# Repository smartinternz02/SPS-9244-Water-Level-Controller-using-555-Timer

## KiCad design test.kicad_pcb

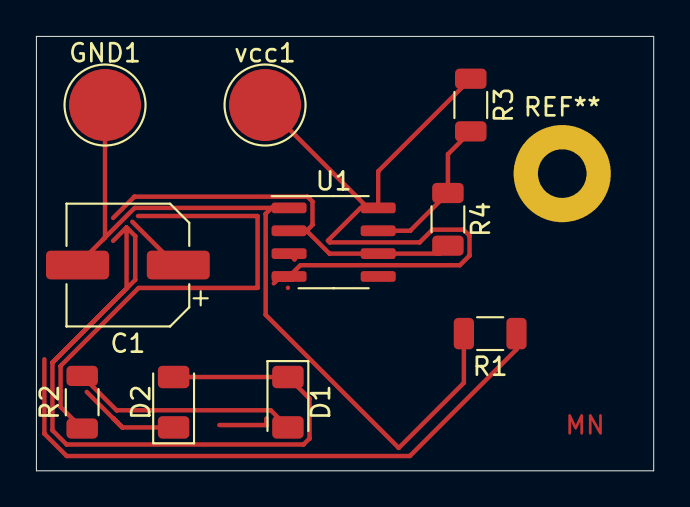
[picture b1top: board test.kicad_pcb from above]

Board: 2 copper layers, 34.3 x 24.1 mm, 10 parts (0 on the bottom side), 7 nets.

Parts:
C1: 10ufd/16V; CP_Elec_6.3x5.2
D1, D2: LED; LED_1206_3216Metric
GND1: GND; TestPoint_Pad_D4.0mm
R1, R2: 470E 1206; R_1206_3216Metric
R3, R4: 150K 1206; R_1206_3216Metric
U1: LM555; SOIC-8_3.9x4.9mm_P1.27mm
vcc1: +9v vcc; TestPoint_Pad_D4.0mm

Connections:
/THRTRG: C1.1, R4.2, U1.2, U1.6
/vcc: R2.1, R3.1, U1.4, U1.8, vcc1.1
GNDREF: C1.2, GND1.1, R1.2, U1.1
unnamed: D1.1, D2.2, U1.3
unnamed: D1.2, R2.2
unnamed: D2.1, R1.1
unnamed: R3.2, R4.1, U1.7
